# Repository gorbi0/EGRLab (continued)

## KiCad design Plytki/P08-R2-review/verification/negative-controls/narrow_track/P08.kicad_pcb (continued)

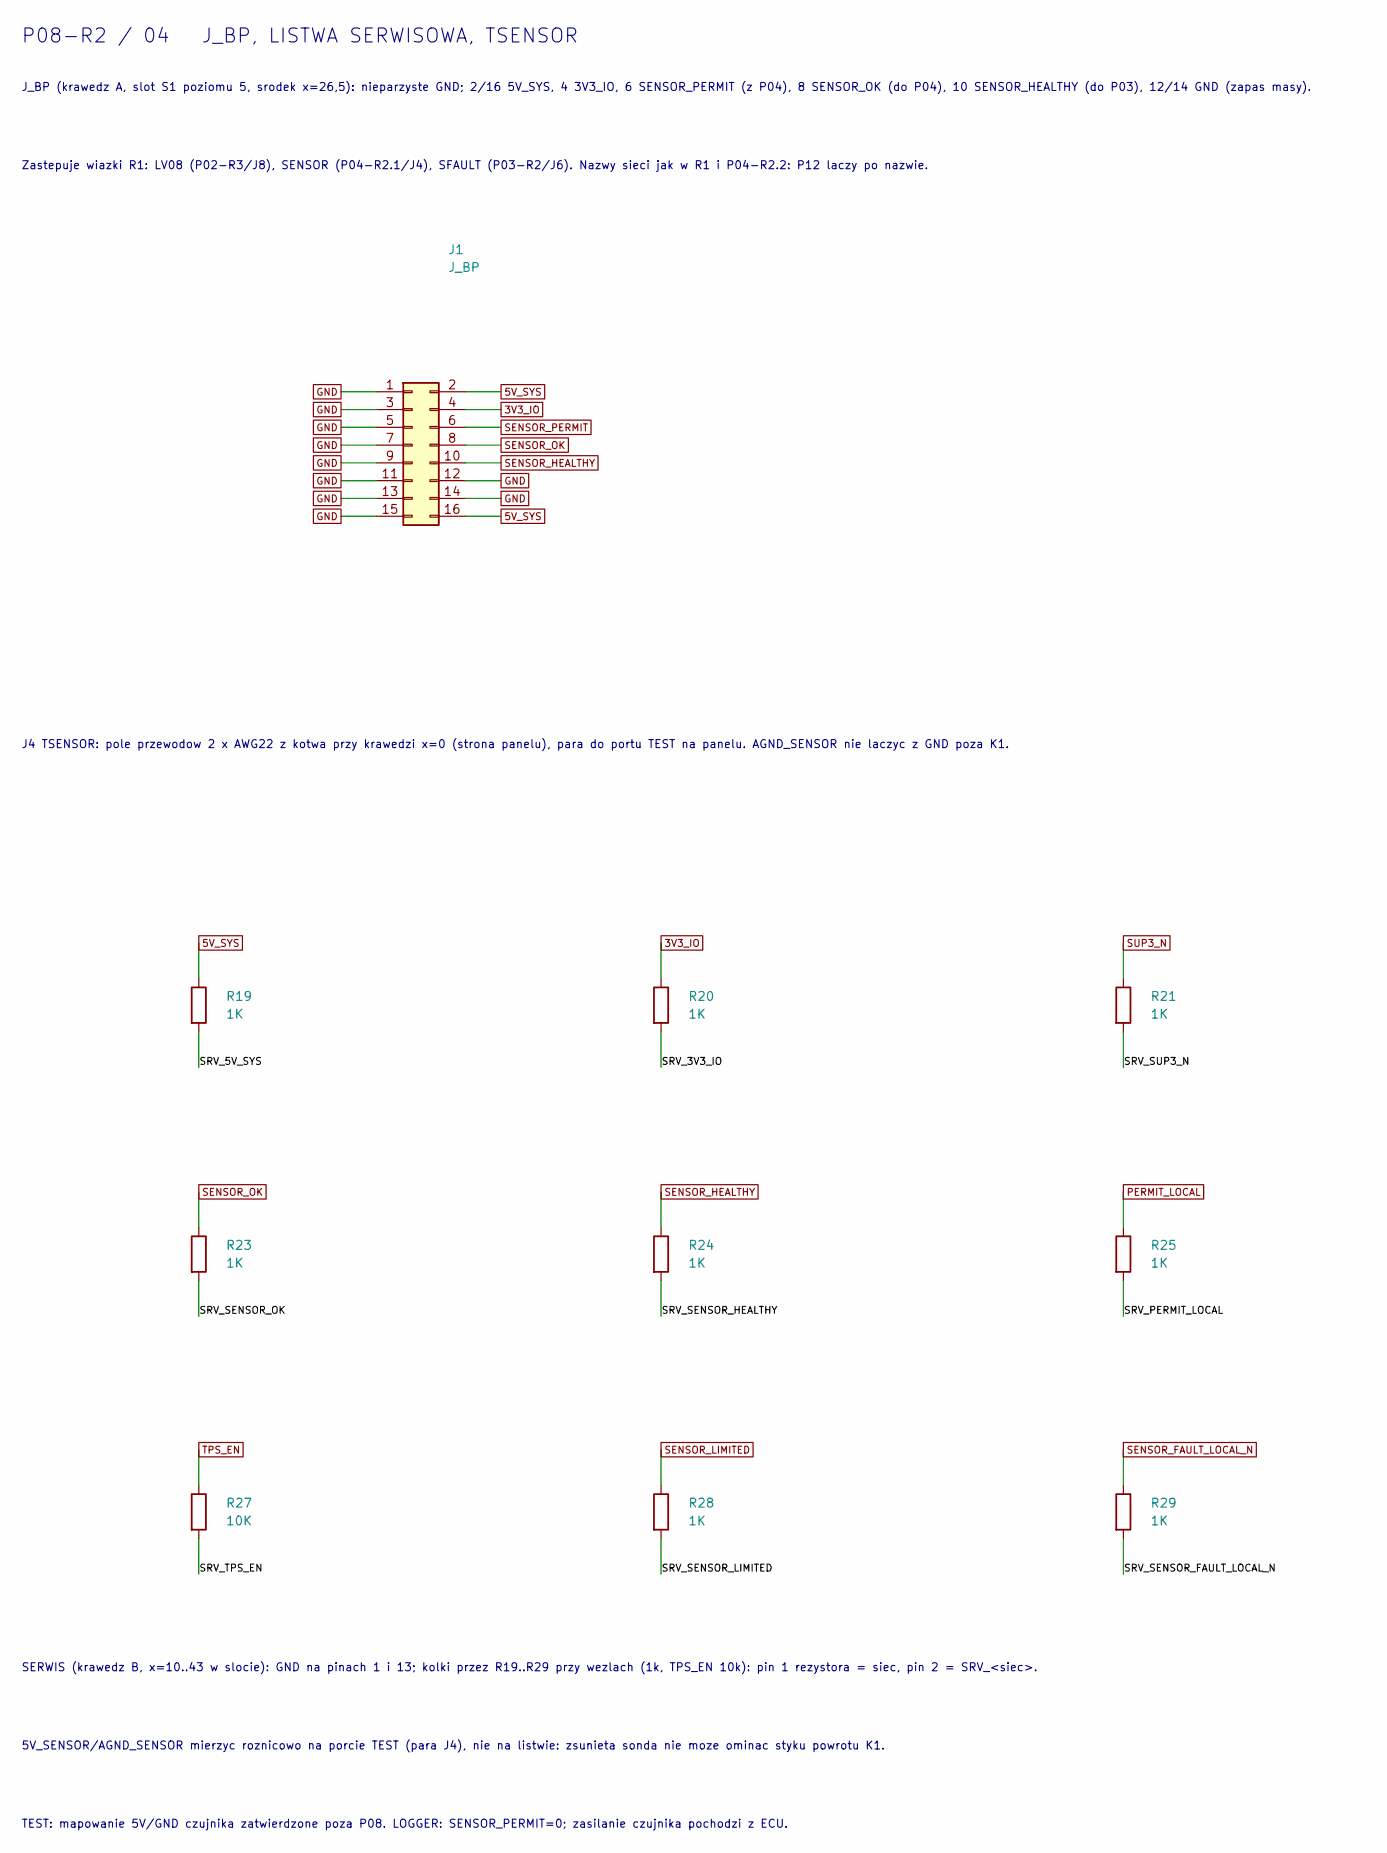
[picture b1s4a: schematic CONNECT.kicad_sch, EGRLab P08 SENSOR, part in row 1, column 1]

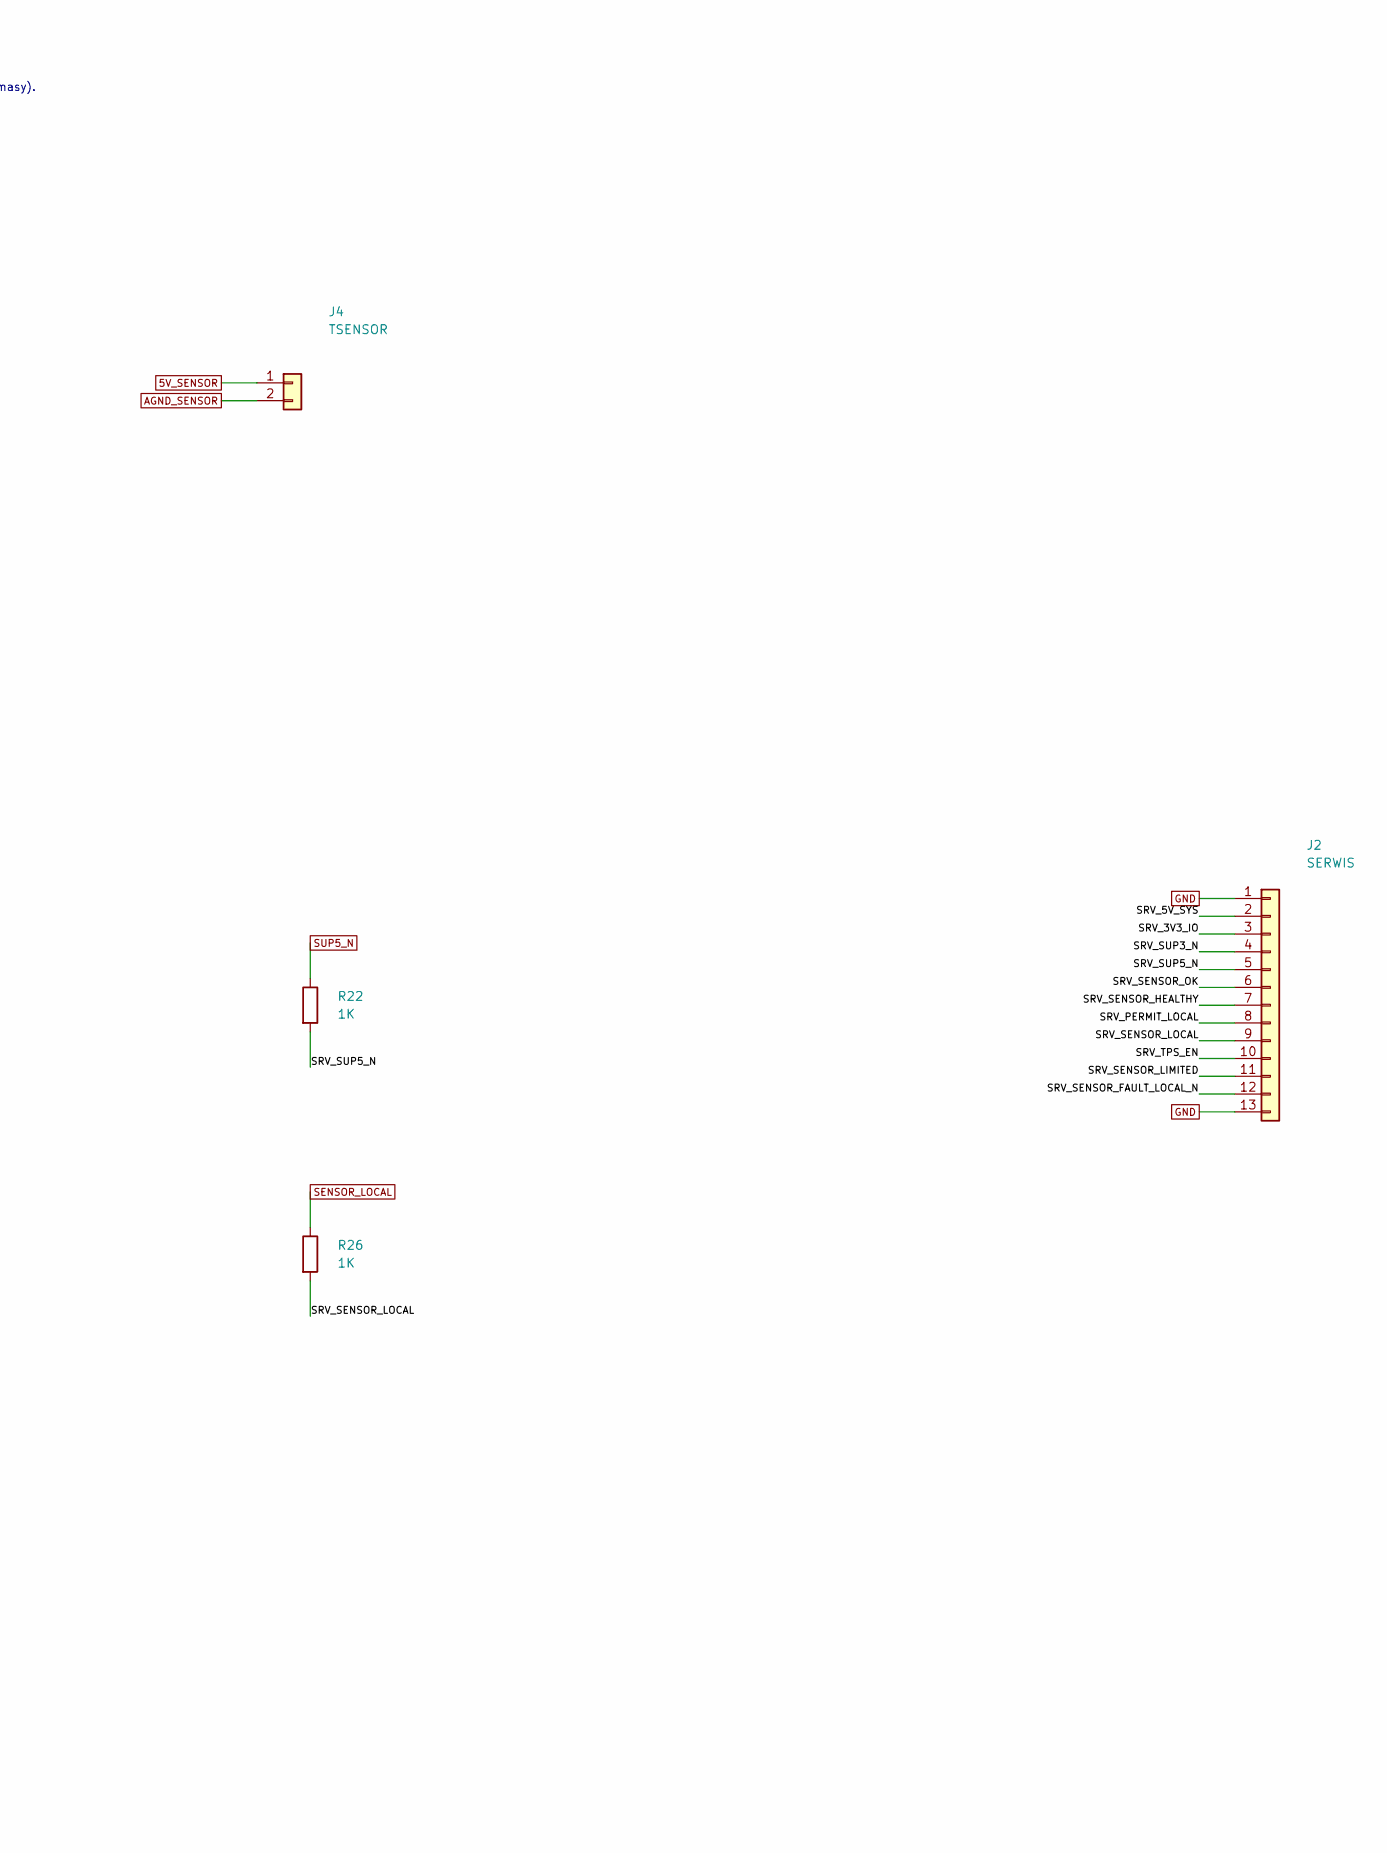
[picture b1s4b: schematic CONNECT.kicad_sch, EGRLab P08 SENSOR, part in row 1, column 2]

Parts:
J1: J_BP; IDC-Header_2x08_P2.54mm_Horizontal; MPN IDC header 2x8 2.54mm angled shrouded, 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
J2: SERWIS; PinHeader_1x13_P2.54mm_Horizontal; MPN Goldpin 1x13 2.54mm angled (buy angled 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
J4: TSENSOR; PTH_TSENSOR_2; MPN 2 x AWG22 soldered, tie anchor 12 mm
R19, R20, R21, R22, R23, R24, R25, R26, R28, R29: 1K; R_1206_3216Metric_Pad1.30x1.75mm_HandSolder; MPN SMD 1206 1% 0.25W 1K
R27: 10K; R_1206_3216Metric_Pad1.30x1.75mm_HandSolder; MPN SMD 1206 1% 0.25W 10K

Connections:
3V3_IO: J1.4, R20.1; also elsewhere on the board
5V_SENSOR: J4.1; also elsewhere on the board
5V_SYS: J1.2, J1.16, R19.1; also elsewhere on the board
/CONNECT/SRV_3V3_IO: J2.3, R20.2
/CONNECT/SRV_5V_SYS: J2.2, R19.2
/CONNECT/SRV_PERMIT_LOCAL: J2.8, R25.2
/CONNECT/SRV_SENSOR_FAULT_LOCAL_N: J2.12, R29.2
/CONNECT/SRV_SENSOR_HEALTHY: J2.7, R24.2
/CONNECT/SRV_SENSOR_LIMITED: J2.11, R28.2
/CONNECT/SRV_SENSOR_LOCAL: J2.9, R26.2
/CONNECT/SRV_SENSOR_OK: J2.6, R23.2
/CONNECT/SRV_SUP3_N: J2.4, R21.2
/CONNECT/SRV_SUP5_N: J2.5, R22.2
/CONNECT/SRV_TPS_EN: J2.10, R27.2
AGND_SENSOR: J4.2; also elsewhere on the board
GND: J1.1, J1.3, J1.5, J1.7, J1.9, J1.11, J1.12, J1.13, J1.14, J1.15, J2.1, J2.13; also elsewhere on the board
PERMIT_LOCAL: R25.1; also elsewhere on the board
SENSOR_FAULT_LOCAL_N: R29.1; also elsewhere on the board
SENSOR_HEALTHY: J1.10, R24.1; also elsewhere on the board
SENSOR_LIMITED: R28.1; also elsewhere on the board
SENSOR_LOCAL: R26.1; also elsewhere on the board
SENSOR_OK: J1.8, R23.1; also elsewhere on the board
SENSOR_PERMIT: J1.6; also elsewhere on the board
SUP3_N: R21.1; also elsewhere on the board
SUP5_N: R22.1; also elsewhere on the board
TPS_EN: R27.1; also elsewhere on the board

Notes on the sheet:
J_BP (krawedz A, slot S1 poziomu 5, srodek x=26,5): nieparzyste GND; 2/16 5V_SYS, 4 3V3_IO, 6 SENSOR_PERMIT (z P04), 8 SENSOR_OK (do P04), 10 SENSOR_HEALTHY (do P03), 12/14 GND (zapas masy).
Zastepuje wiazki R1: LV08 (P02-R3/J8), SENSOR (P04-R2.1/J4), SFAULT (P03-R2/J6). Nazwy sieci jak w R1 i P04-R2.2: P12 laczy po nazwie.
J4 TSENSOR: pole przewodow 2 x AWG22 z kotwa przy krawedzi x=0 (strona panelu), para do portu TEST na panelu. AGND_SENSOR nie laczyc z GND poza K1.
SERWIS (krawedz B, x=10..43 w slocie): GND na pinach 1 i 13; kolki przez R19..R29 przy wezlach (1k, TPS_EN 10k): pin 1 rezystora = siec, pin 2 = SRV_<siec>.
5V_SENSOR/AGND_SENSOR mierzyc roznicowo na porcie TEST (para J4), nie na listwie: zsunieta sonda nie moze ominac styku powrotu K1.
TEST: mapowanie 5V/GND czujnika zatwierdzone poza P08. LOGGER: SENSOR_PERMIT=0; zasilanie czujnika pochodzi z ECU.
P08-R2 / 04 J_BP, LISTWA SERWISOWA, TSENSOR

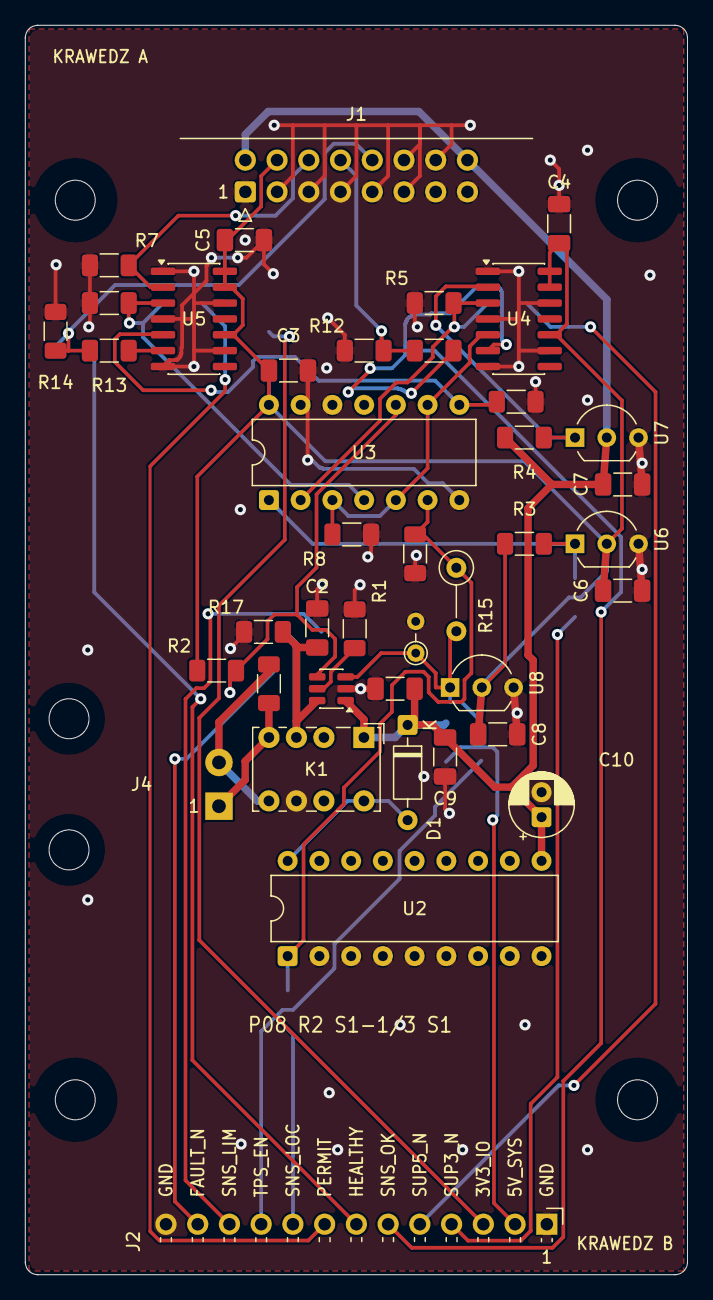
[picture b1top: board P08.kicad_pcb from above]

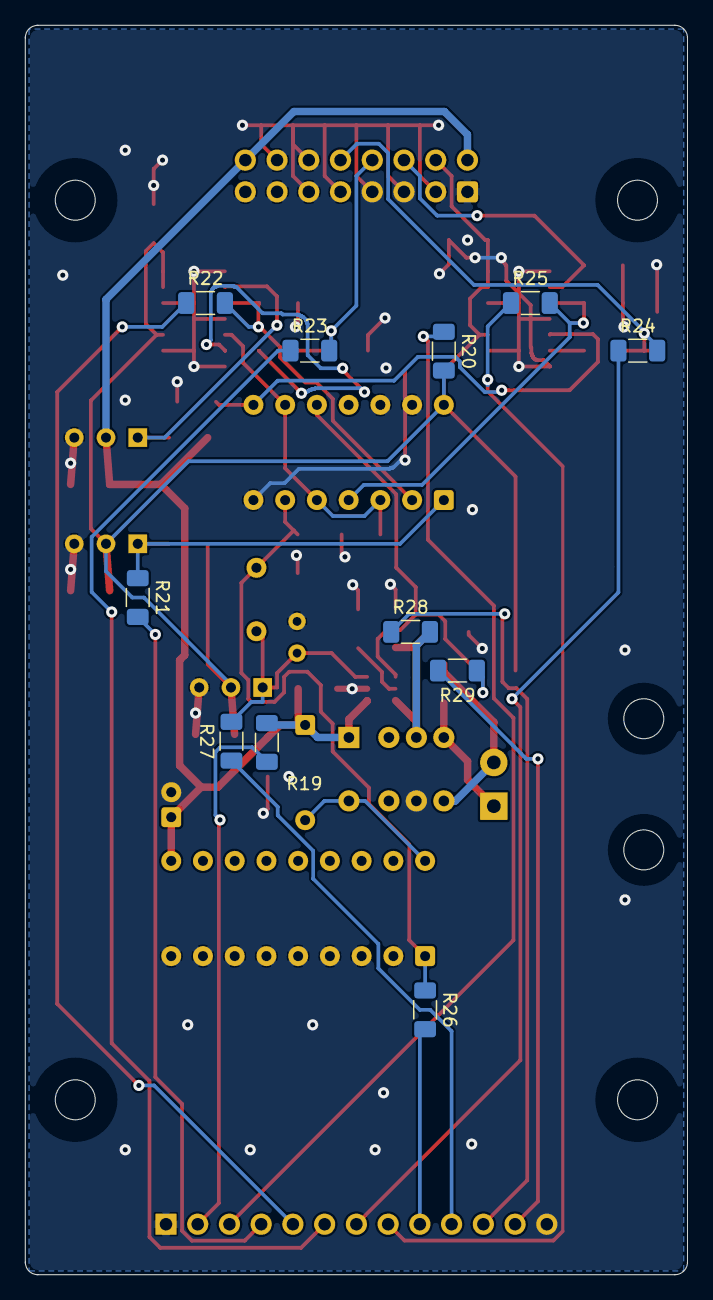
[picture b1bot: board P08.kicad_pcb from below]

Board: 2 copper layers, 53.0 x 100.0 mm, 56 parts (11 on the bottom side), 33 nets.

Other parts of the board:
H1, H2, H3, H4: M3 NPTH
